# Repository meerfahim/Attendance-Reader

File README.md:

# Attendance-Reader

This project is created for a client who is developing an attendance reader. In this project, I have designed the schematic and the PCB for the system and delivered it to the client.

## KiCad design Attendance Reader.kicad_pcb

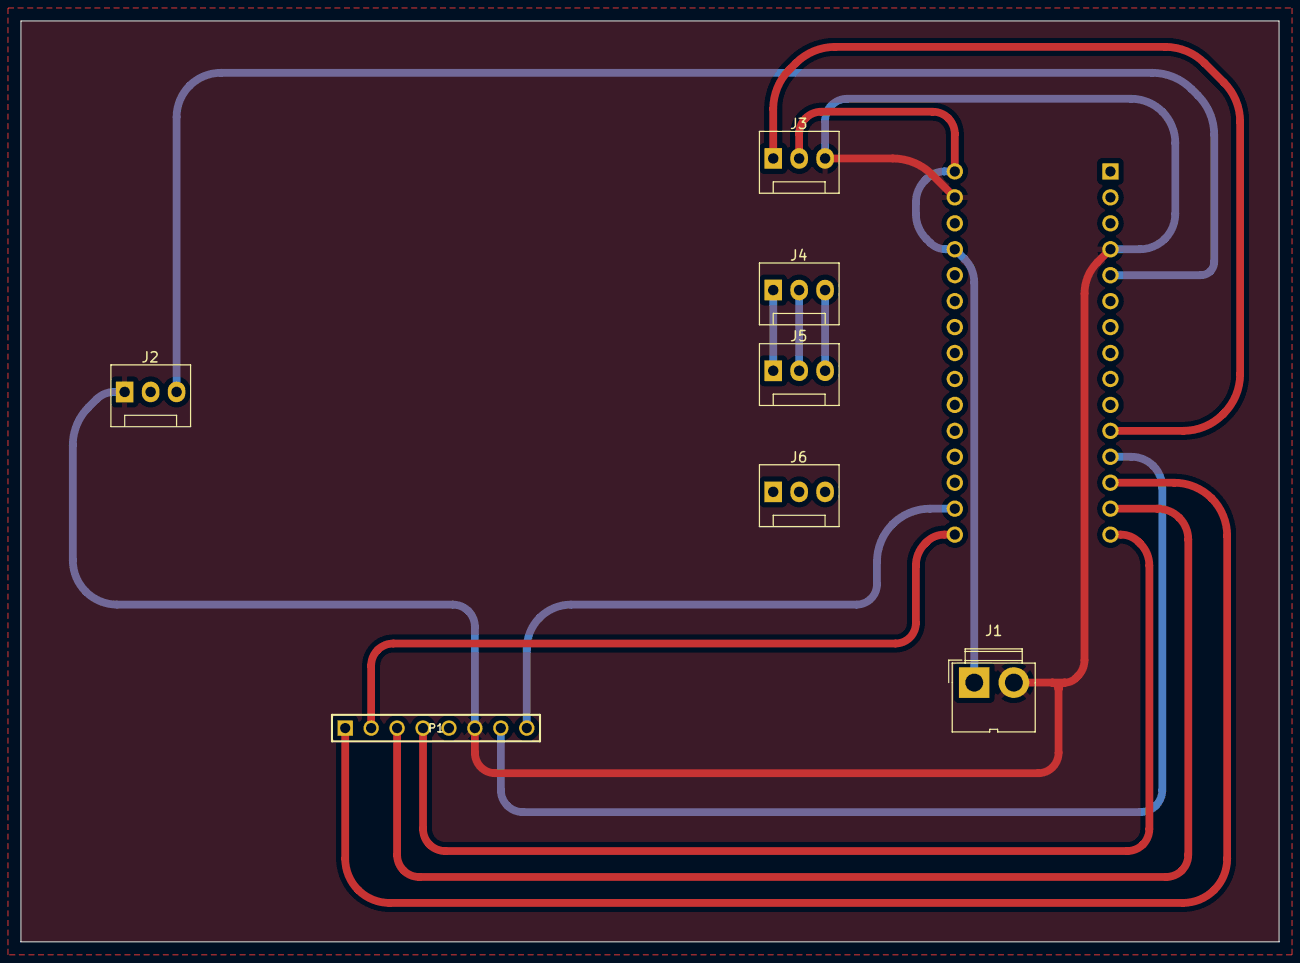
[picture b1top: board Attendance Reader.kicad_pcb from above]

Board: 2 copper layers, 123.2 x 90.2 mm, 8 parts (1 on the bottom side), 13 nets.

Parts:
A1: Arduino_Nano_v3.x; Arduino_Nano
J1: Vcc; JWT_A3963_1x02_P3.96mm_Vertical
J2: GND_B; FanPinHeader_1x03_P2.54mm_Vertical
J3: GND; FanPinHeader_1x03_P2.54mm_Vertical
J4: Vcc; FanPinHeader_1x03_P2.54mm_Vertical
J5: D8; FanPinHeader_1x03_P2.54mm_Vertical
J6: Conn_01x03_Pin; FanPinHeader_1x03_P2.54mm_Vertical
P1: RFID-RC522-MODULE; RFID-RC522

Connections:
GND: A1.4 (GND), A1.29 (GND), J1.2, J2.1, J3.3, P1.6 (GND)
unnamed: A1.17 (3V3), P1.8 (3.3V)
unnamed: A1.5 (D2), J2.3
unnamed: A1.11 (D8), J3.1
unnamed: A1.12 (D9), P1.7 (RST)
unnamed: A1.13 (D10), P1.1 (SDA)
unnamed: A1.14 (D11), P1.3 (MOSI)
unnamed: A1.15 (D12), P1.4 (MISO)
unnamed: A1.16 (D13), P1.2 (SCK)
unnamed: J4.1, J5.1
unnamed: J4.2, J5.2
unnamed: J4.3, J5.3
VCC: A1.27 (+5V), A1.30 (VIN), J1.1, J3.2
